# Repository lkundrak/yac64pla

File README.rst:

yac64pla -- Yet Another PLD-based C64 PLA replacement
=====================================================

TLDR: This is a derivative of `c64pla`_, the C64 PLA replacement project that
utilizes dual GAL chips. This one uses PLCC28 packages instead of DIL32
and that's basically it.

PLA replacements and the original c64pla
----------------------------------------

For as long as C64 PLA chips like to fail, clever people have been finding
ways to replace them.

In my opinion, the cheapest and most elegant approach was taken by Daniël
Mantione: replace the original, difficult to obtain, logic array with a pair
of slightly smaller GAL programmable logic chips. Cheap, simple and reliable.

Now stop reading and read the documentation of Daniël's `c64pla`_ first.

.. _c64pla: https://www.freepascal.org/~daniel/c64pla/

Really. This document assumes you've read the above. From this point on,
it only deals with what's different in my version.

Why this project exists
-----------------------

The only problem I saw with the original project is that it's not pretty.
The pair of long, thin and noodly DIL24 packages obscenely extends to the
sides, angering the gods and completely ruining the feng-shui of the general area.

I set out to it fix and ended up replace the DIL 24 parts with much tinier
PLCC 28 footprints, so that the board will not be larger than an usunal DIL part.

That's it. If you don't care about the looks, or like the dual-DIL looks of
the original, use the original project. This one is not objectively better.

The board
---------

.. image:: yac64pla-brd.jpeg
   :width: 640px

.. image:: yac64pla-render.png
   :width: 640px

Schematic
---------

.. image:: yac64pla-sch.svg
   :width: 1280px

Parts
-----

GAL (and compatible ATF) family devices that use PLCC-28 can be used.
In particular, that's GAL20V8, GAL22V10, ATF20V8 or ATF22V10.

Building it
-----------

1. Order the PCB. With the KiCAD's PCBway and JLC plugis (perhaps others),
   it's really little more than one click away.

2. Program the JED files on to the PLDs. I use the TL866-II programmer with
   the `minipro`_ tool. You'll also need the PLCC-28 to DIL-24 adapter.

   The repository contains the pre-built JED files for individual chips of
   supported device families:

   yac64pla-top-20V8.jed
      Top chip programming for GAL20V8 or ATF20V8 devices.

   yac64pla-bot-20V8.jed
      Bottom chip programming for GAL20V8 or ATF20V8 devices.

   yac64pla-top-22V10.jed
      Top chip programming for GAL22V10 or ATF22V10 devices.

   yac64pla-bot-22V10.jed
      Bottom chip programming for GAL22V10 or ATF22V10 devices.

3. Solder it. Even though there are SMD parts, they're large enough for
   them not to be difficult to hand-solder.

.. _minipro: https://gitlab.com/DavidGriffith/minipro

Should you need any help, find out if there's a Hackerspace in your area.
You're certain to find someone who's going to help you acquire the skills
you need.

You may try dropping me a message. I'd be happy to help but note I haven't
figured out how not to suck at e-mail yet.

PLD programming
---------------

The c64pla is programmed with WinCUPL. Thus sucks, because while it's
feature rich, it's pretty terrible, aged and proprietary tool. Also, I don't
really know how to use it. I redid it in GALasm format, which can be
compiled by `galette`_, a modern free software tool. It's much simpler, but
perfectly appropriate for the job.

.. _galette: https://github.com/simon-frankau/galette

Apart from a rewrite in GALasm, I created a Perl script that can regenerate
the GALasm files for different pin layout and move the logic equations
across the chips. It also updates the KiCAD schematic, ensuring the PCB
stays up to date. This is probably not too useful now, but it enabled me to
shuffle pins around when choosing a good enough pin layout for the tight
routing on the small PCB.

Licensing
---------

Given how ignorant am I about legal aspect of the project, and how unlikely
are the lawyers to knock on my door and take everything that's dear to me,
I decided to not give a shit.

I'm placing the parts of the project I've done into the Public Domain.

Love,
Lubo

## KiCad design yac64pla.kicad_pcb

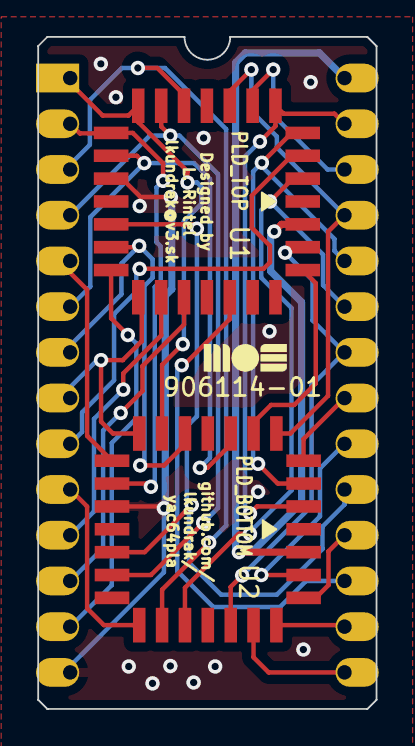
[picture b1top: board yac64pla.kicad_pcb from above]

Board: 2 copper layers, 18.8 x 37.3 mm, 3 parts (0 on the bottom side), 29 nets.

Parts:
U1: PLD_TOP; PLCC-28
U2: PLD_BOTTOM; PLCC-28
U3: C64_PLA; DIP-28_W15.24mm_Socket_LongPads

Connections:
/A12: U1.5 (I5), U2.2 (I2/CLK), U3.27 (I8/A12)
/A13: U1.12 (I12), U2.13 (I13), U3.2 (I7/A13)
/A14: U1.9 (I9), U2.20 (I020), U3.3 (I6/A14)
/A15: U1.10 (I10), U2.17 (I17), U3.4 (I5/A15)
/BA: U1.6 (I6), U3.26 (I9/BA)
/FE: U1.11 (I11), U2.10 (I10), U3.1 (FE/NC)
/GR/~W: U1.18 (IO18), U3.13 (F4/GR/~W)
/R/~W: U1.4 (I4), U2.3 (I3), U3.24 (I11/R/~W)
/TCR: U1.26 (IO26), U2.6 (I6)
/VA12: U2.27 (I27), U3.20 (I15/VA12)
/VA13: U2.4 (I4), U3.21 (I14/VA13)
/~AEC: U1.7 (I7), U2.5 (I5), U3.25 (I10/~AEC)
/~BASIC: U1.23 (IO23), U3.17 (F1/~BASIC)
/~CASRAM: U2.26 (IO26), U3.18 (F0/~CASRAM)
/~CAS: U1.3 (I3), U3.9 (I0/~CAS)
/~CHAREN: U1.13 (I13), U2.7 (I7), U3.6 (I3/~CHAREN)
/~CHAROM: U2.24 (IO24), U3.15 (F3/~CHAROM)
/~EXROM: U1.2 (I2/CLK), U2.21 (IO21), U3.23 (I12/~EXROM)
/~GAME: U1.27 (I27), U2.23 (IO23), U3.22 (I13/~GAME)
/~IRAM: U1.17 (I17), U2.9 (I9), U3.7 (I2/~IRAM)
/~I/O: U1.21 (IO21), U3.12 (F5/~I/O)
/~KERNAL: U2.25 (IO25), U3.16 (F2/~KERNAL)
/~LORAM: U1.19 (IO19), U2.11 (I11), U3.8 (I1/~LORAM)
/~OE: U1.16 (I16/~OE), U2.16 (I16/~OE), U3.19 (~OE)
/~ROMH: U2.19 (IO19), U3.10 (F7/~ROMH)
/~ROML: U1.20 (I020), U3.11 (F6/~ROML)
/~VA14: U2.12 (I12), U3.5 (I4/~VA14)
GND: U1.14 (GND), U2.14 (GND), U3.14 (VSS)
VCC: U1.28 (VCC), U2.28 (VCC), U3.28 (VCC)

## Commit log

2023-01-08 Initial revision
2024-03-04 Add GAL22V10/ATF22V10 support
2024-03-04 Rename left/right to top/bottom
2024-03-04 Slight layout improvements
2024-04-10 Boards made, tested
